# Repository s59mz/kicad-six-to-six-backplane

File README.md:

# kicad-six-to-six-backplane
Backplane board for Six-to-six RF splitter/combiner

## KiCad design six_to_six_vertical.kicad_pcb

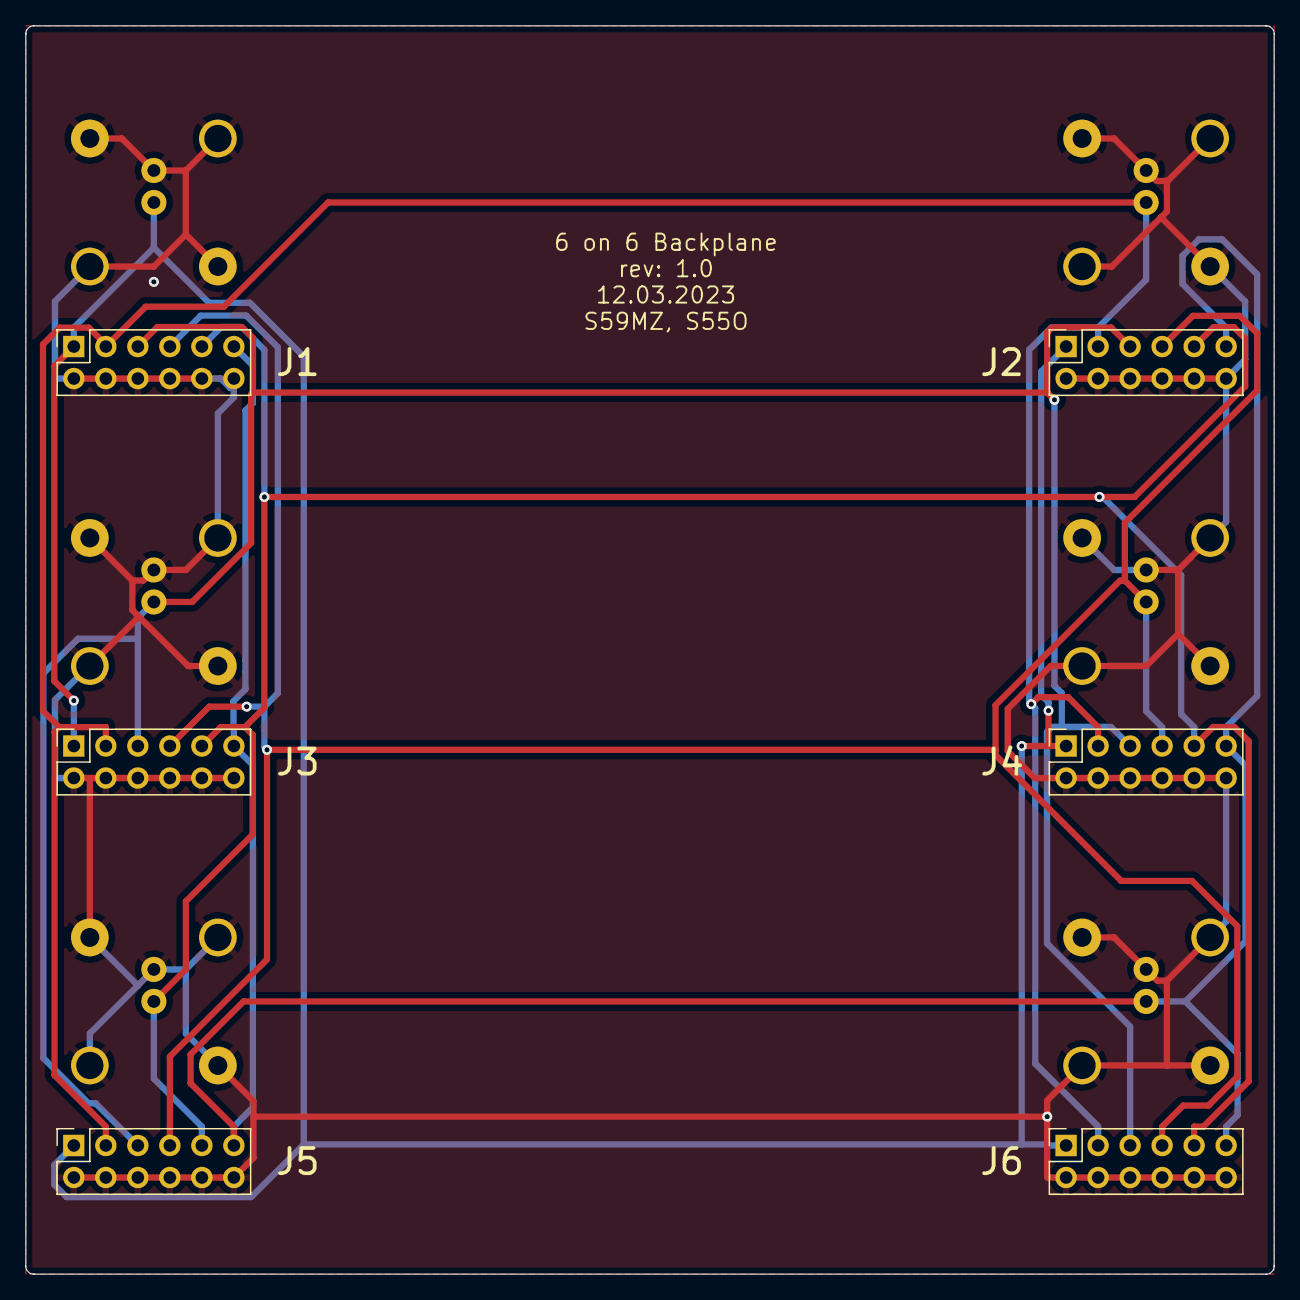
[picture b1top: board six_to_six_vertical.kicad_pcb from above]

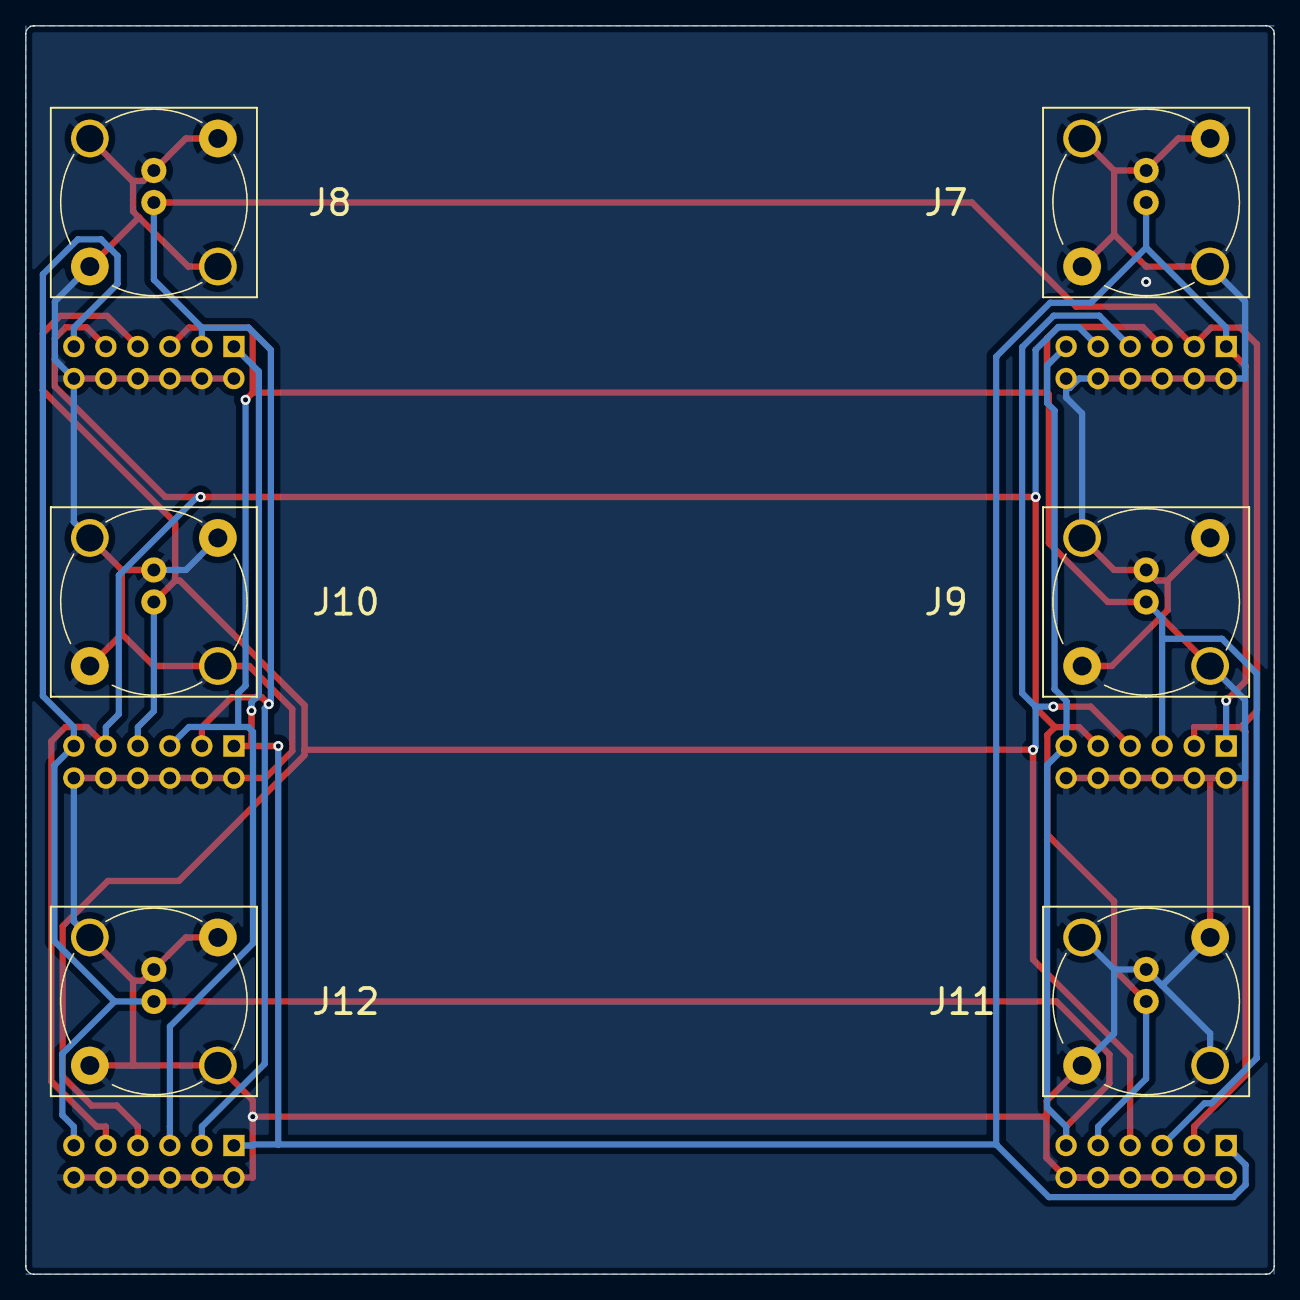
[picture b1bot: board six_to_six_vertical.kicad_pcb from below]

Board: 2 copper layers, 99.1 x 99.1 mm, 12 parts (6 on the bottom side), 7 nets.

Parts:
J1, J2, J3, J4, J5, J6: RF Conn; PinSocket_2x06_P2.54mm_Vertical
J7, J8, J9, J10, J11, J12: bnc; BNC_vertical

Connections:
/rf-1: J1.1, J2.1, J3.1, J4.1, J5.1, J6.1, J7.1 (In)
/rf-2: J1.3, J2.3, J3.3, J4.3, J5.3, J6.3, J8.1 (In)
/rf-3: J1.5, J2.5, J3.5, J4.5, J5.5, J6.5, J9.1 (In)
/rf-4: J1.7, J2.7, J3.7, J4.7, J5.7, J6.7, J10.1 (In)
/rf-5: J1.9, J2.9, J3.9, J4.9, J5.9, J6.9, J11.1 (In)
/rf-6: J1.11, J2.11, J3.11, J4.11, J5.11, J6.11, J12.1 (In)
GND: J1.2, J1.4, J1.6, J1.8, J1.10, J1.12, J2.2, J2.4, J2.6, J2.8, J2.10, J2.12, J3.2, J3.4, J3.6, J3.8, J3.10, J3.12, J4.2, J4.4, J4.6, J4.8, J4.10, J4.12, J5.2, J5.4, J5.6, J5.8, J5.10, J5.12, J6.2, J6.4, J6.6, J6.8, J6.10, J6.12, J7.2 (Ext), J8.2 (Ext), J9.2 (Ext), J10.2 (Ext), J11.2 (Ext), J12.2 (Ext)

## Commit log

2023-03-12 added BOM and jpg snapshot
2023-03-15 renumber connectors
2023-03-20 fixed RF board distances to fit on 30mm spacers
2023-03-22 added BNC part number
2023-03-27 update board name
